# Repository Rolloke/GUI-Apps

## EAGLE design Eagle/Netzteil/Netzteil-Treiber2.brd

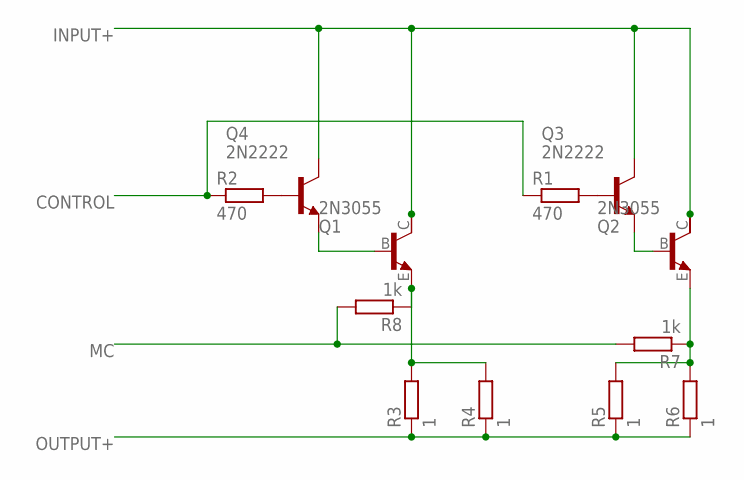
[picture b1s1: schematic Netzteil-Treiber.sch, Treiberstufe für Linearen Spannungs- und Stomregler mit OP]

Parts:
Q1, Q2: 2N3055; TO3
Q3, Q4: 2N2222; TO18
R1, R2: 470; 0207/12
R3, R4, R5, R6: 1; 0207/12
R7, R8: 1k; 0207/12

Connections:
CONTROL: R1.1, R2.1
INPUT+: Q1.C, Q2.C, Q3.3 (C), Q4.3 (C)
MC: R7.2, R8.2
unnamed: Q3.2 (B), R1.2
unnamed: Q4.2 (B), R2.2
unnamed: Q1.E, R3.2, R4.2, R8.1
unnamed: Q1.B, Q4.1 (E)
unnamed: Q2.B, Q3.1 (E)
unnamed: Q2.E, R5.2, R6.2, R7.1
OUTPUT+: R3.1, R4.1, R5.1, R6.1

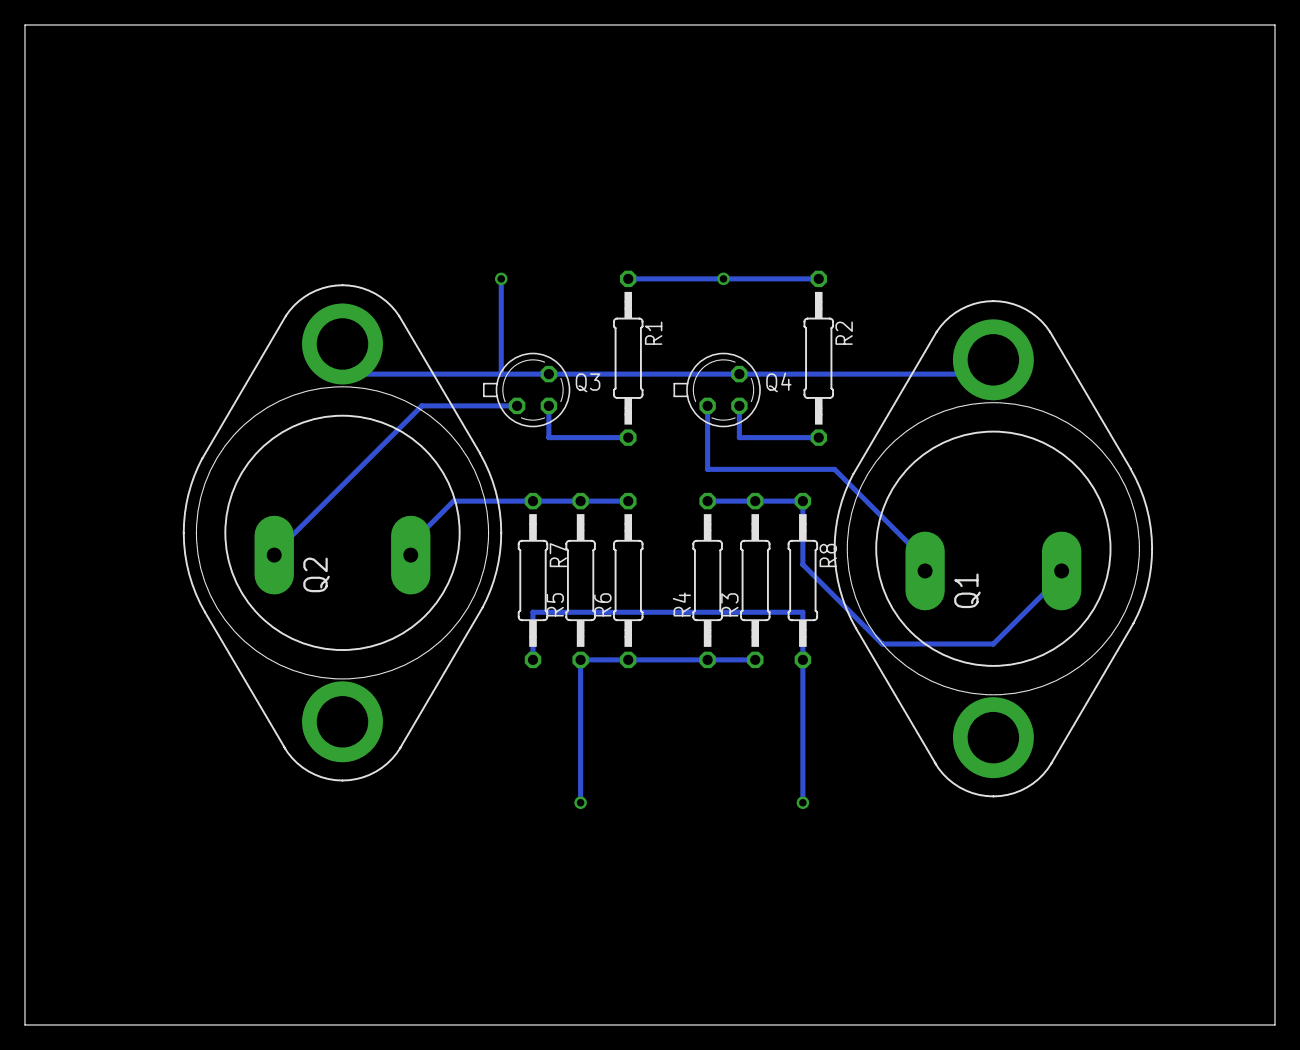
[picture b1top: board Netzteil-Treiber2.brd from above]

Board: 2 copper layers, 100.0 x 80.0 mm, 12 parts (0 on the bottom side), 10 nets.

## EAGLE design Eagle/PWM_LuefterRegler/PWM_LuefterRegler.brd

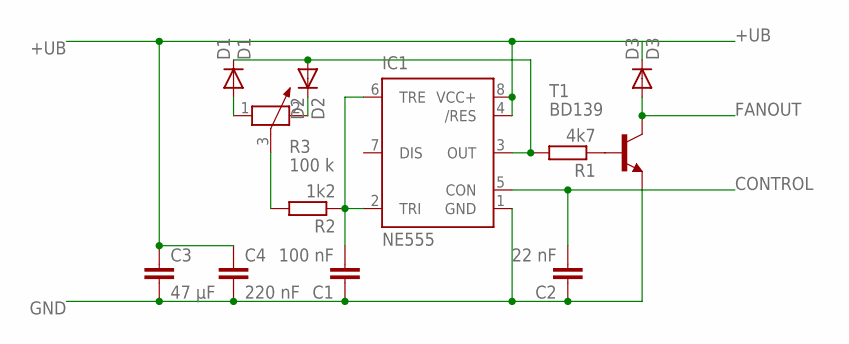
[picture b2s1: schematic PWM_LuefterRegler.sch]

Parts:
C1: 100 nF; C2.5-3
C2: 22 nF; C7.5B3
C3: 47 µF; C5B4.5
C4: 220 nF; C7.5B3
D1: D1; DO35-10
D2: D2; DO35-10
D3: D3; DO35-10
IC1: NE555; DIL-08
R1: 4k7; 0207/10
R2: 1k2; 0207/10
R3: 100 k; PT-10
T1: BD139; TO126

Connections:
+UB: C3.1, C4.1, D3.C, IC1.4 (/RES), IC1.8 (VCC+)
CONTROL: C2.2, IC1.5 (CON)
FANOUT: D3.A, T1.2 (C)
GND: C1.1, C2.1, C3.2, C4.2, IC1.1 (GND), T1.1 (E)
unnamed: C1.2, IC1.2 (TRI), IC1.6 (TRE), R2.1
unnamed: D2.C, R3.2
unnamed: R2.2, R3.3
unnamed: D1.A, R3.1
unnamed: D1.C, D2.A, IC1.3 (OUT), R1.2
unnamed: R1.1, T1.3 (B)

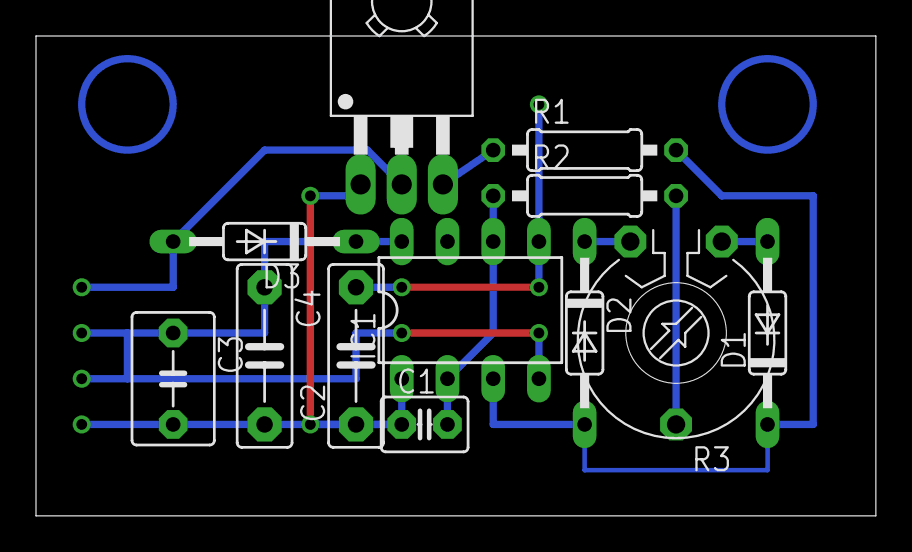
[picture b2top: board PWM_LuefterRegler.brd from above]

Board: 2 copper layers, 46.7 x 26.7 mm, 12 parts (0 on the bottom side), 10 nets.

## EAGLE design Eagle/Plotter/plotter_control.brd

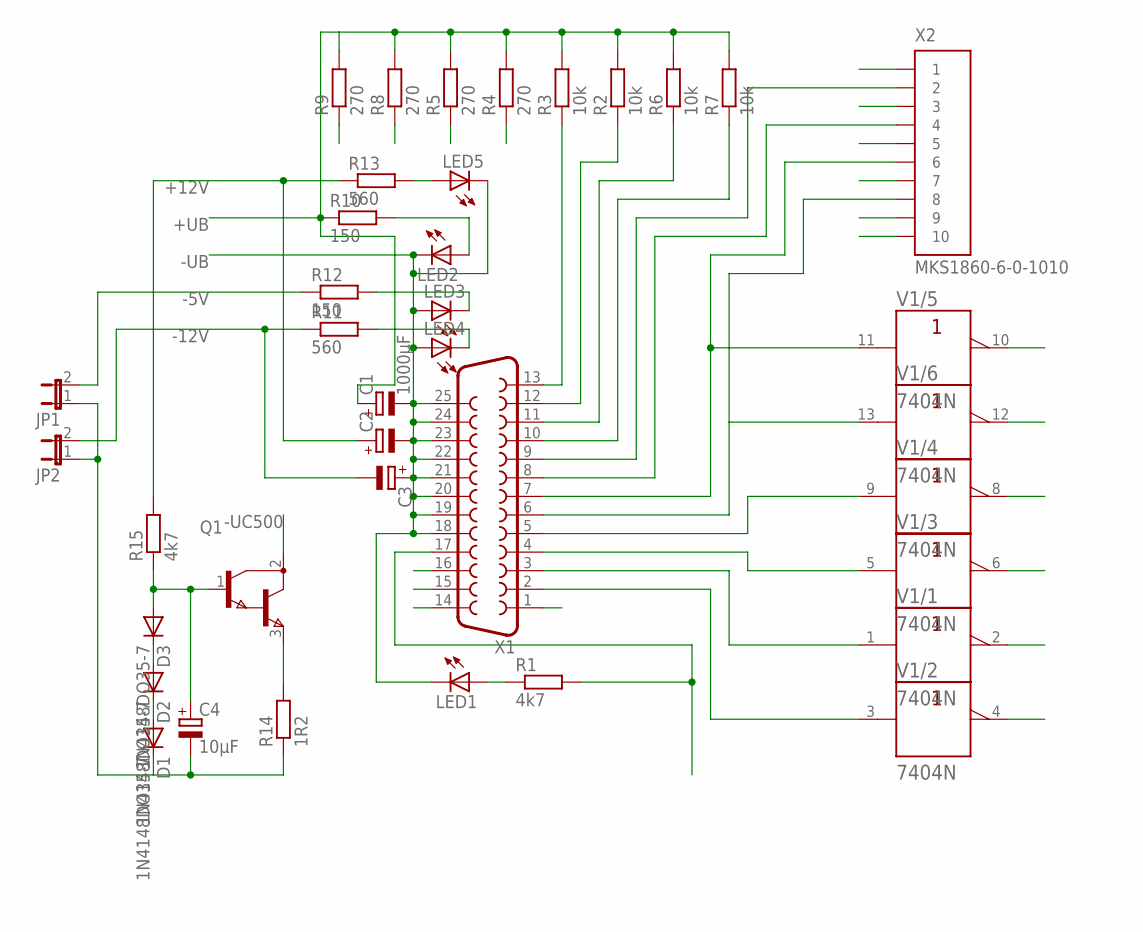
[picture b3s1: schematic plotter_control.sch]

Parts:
C1: 1000µF; E5-8,5
C2, C3: CPOL-EUE5-8.5; E5-8,5
C4: 10µF; E2,5-5
D1, D2, D3: 1N4148DO35-7; DO35-7
JP1, JP2: JP1E; JP1
LED1, LED2, LED3, LED4, LED5: LED3MM
Q1: BD647; TO220
R1, R15: 4k7; 0204/7
R2, R3, R6, R7: 10k; 0204/7
R4, R5, R8, R9: 270; 0204/7
R10: 150; 0207/15
R11, R13: 560; 0204/7
R12: 150; 0207/10
R14: 1R2; 0204/7
V1: 7404N; DIL14
X1: F25HP
X2: MKS1860-6-0-1010

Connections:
+12V: C2.+, R13.1, R15.2
+UB: C1.+, R2.2, R3.2, R4.2, R5.2, R6.2, R7.2, R8.2, R9.2, R10.1, V1.14 (+UB)
-5V: JP1.2, R12.1
-12V: C3.-, JP2.2, R11.1
-UB: C1.-, C2.-, C3.+, LED1.K (C), LED2.K (C), LED3.A, LED4.A, LED5.K (C), V1.7 (-UB), X1.18, X1.19, X1.20, X1.21, X1.22, X1.23, X1.24, X1.25, X2.1, X2.10
-UC500: Q1.2 (C)
-USERVO: C4.-, D1.C, JP1.1, JP2.1, R14.1
BIT7: X1.8, X2.4
BIT8: X1.9, X2.2
BOTTOM_END: R3.1, X1.13
BOTTOM_LED: R4.1
ENABLE_MOTOR: R1.2, X1.17
ERROR: X1.15
INIT_PRINTER: X1.16
LEFT_END: R7.1, X1.10
LEFT_LED: R9.1
M1_1+: V1.3 (A), X1.2
M1_1-: V1.4 (Y)
M1_2+: V1.1 (A), X1.3
M1_2-: V1.2 (Y)
M2_1+: V1.5 (A), X1.4
M2_1-: V1.6 (Y)
M2_2+: V1.9 (A), X1.5
M2_2-: V1.8 (Y)
M3_1+: V1.13 (A), X1.6, X2.8
M3_1-: V1.12 (Y)
M3_2+: V1.11 (A), X1.7, X2.6
M3_2-: V1.10 (Y)
M4_1: X2.9
M4_2: X2.7
M4_3: X2.5
M4_4: X2.3
MOTOR_COIL1: X1.1
MOTOR_COIL2: X1.14
unnamed: LED1.A, R1.1
unnamed: LED2.A, R10.2
unnamed: LED5.A, R13.2
unnamed: LED3.K (C), R12.2
unnamed: LED4.K (C), R11.2
unnamed: D1.A, D2.C
unnamed: D2.A, D3.C
unnamed: Q1.3 (E), R14.2
unnamed: C4.+, D3.A, Q1.1 (B), R15.1
RIGHT_END: R6.1, X1.11
RIGHT_LED: R8.1
TOP_END: R2.1, X1.12
TOP_LED: R5.1

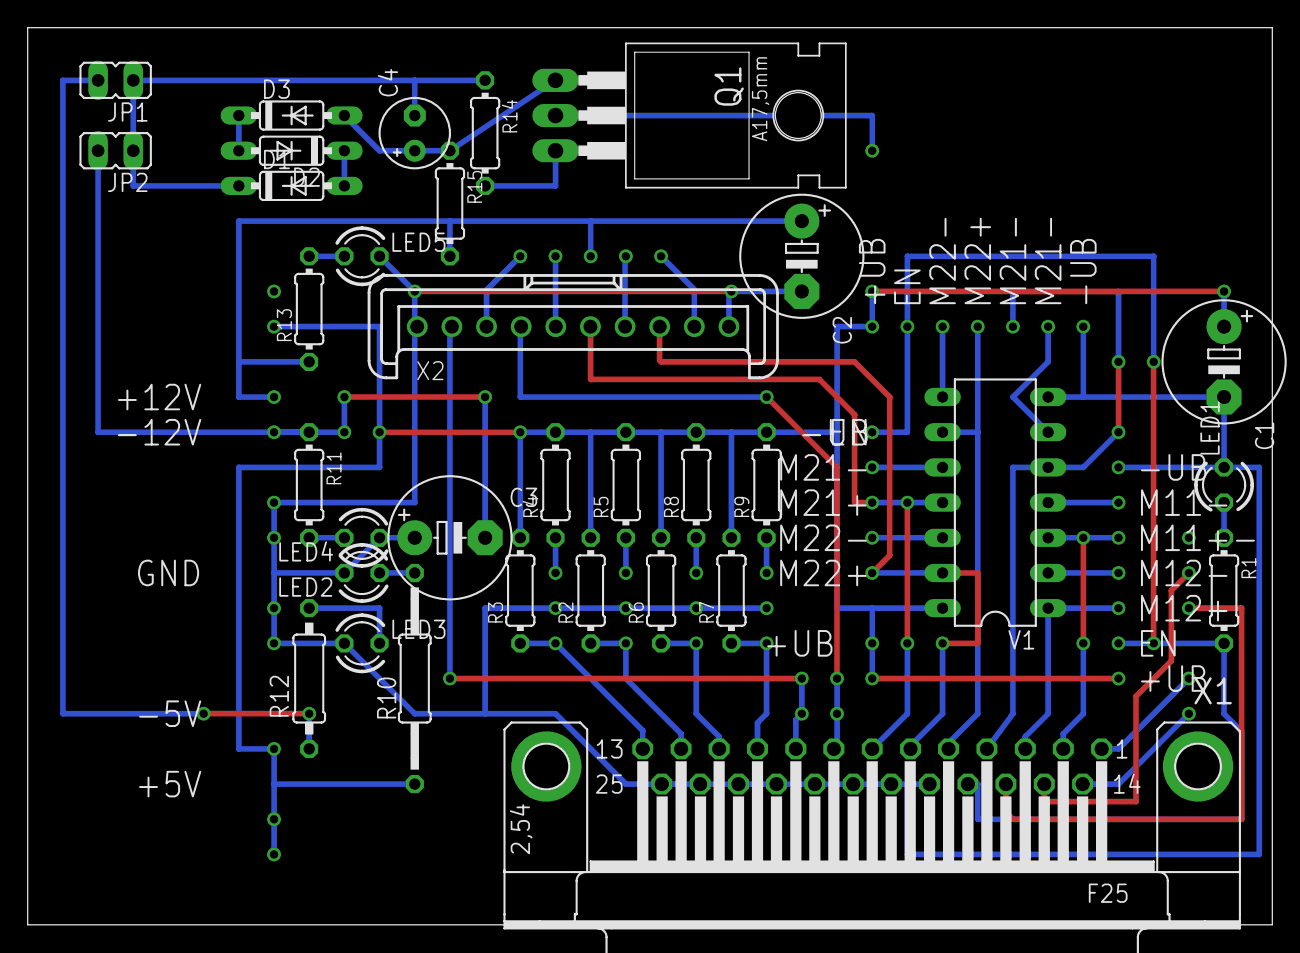
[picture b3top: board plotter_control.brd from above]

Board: 2 copper layers, 89.8 x 64.8 mm, 33 parts (0 on the bottom side), 28 nets.

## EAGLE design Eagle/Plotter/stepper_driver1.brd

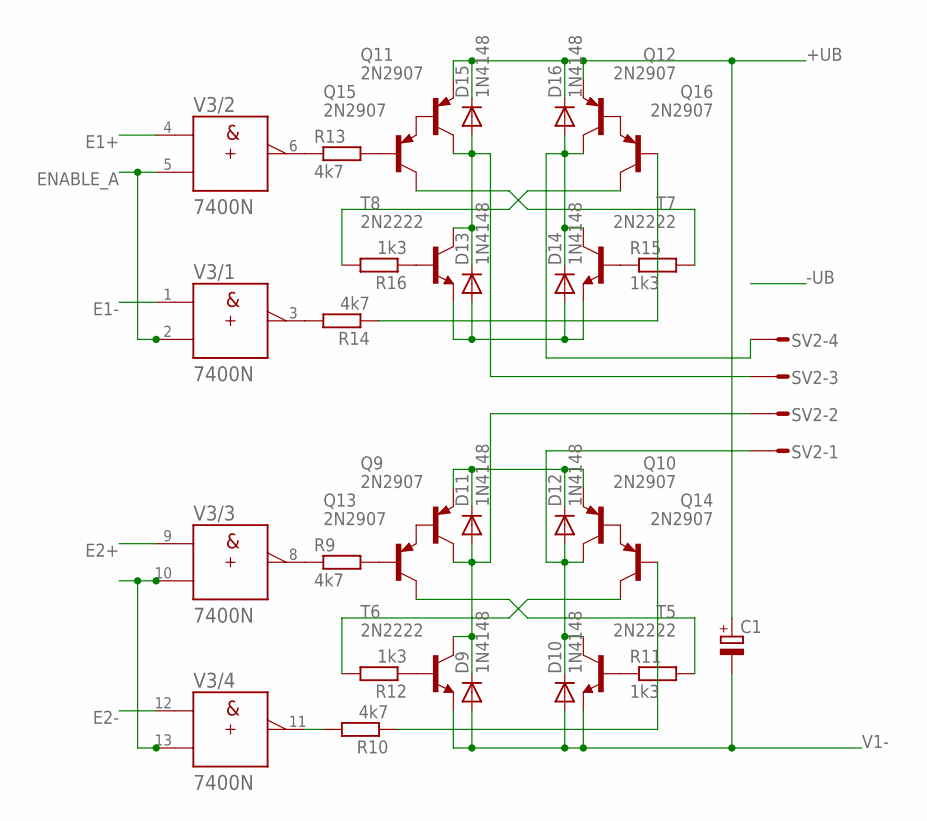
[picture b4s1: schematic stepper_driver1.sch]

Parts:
C1: CPOL-EUE3.5-10; E3,5-10
D9, D10, D11, D12, D13, D14, D15, D16: 1N4148; D-2.5
Q9, Q10, Q11, Q12, Q13, Q14, Q15, Q16: 2N2907; TO18
R9, R13, R14: 4k7; 0207/10
R10: 4k7; 0207/12
R11, R12, R15, R16: 1k3; 0207/10
SV2: S04P
T5, T6, T7, T8: 2N2222; TO18
V3: 7400N; DIL14

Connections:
+UB: C1.+, D11.C, D12.C, D15.C, D16.C, Q9.1 (E), Q10.1 (E), Q11.1 (E), Q12.1 (E), V3.14 (+UB)
-UB: V3.7 (-UB)
A1+: D13.C, D15.A, Q11.3 (C), SV2.3, T8.3 (C)
A1-: D14.C, D16.A, Q12.3 (C), SV2.4, T7.3 (C)
A2+: D9.C, D11.A, Q9.3 (C), SV2.2, T6.3 (C)
A2-: D10.C, D12.A, Q10.3 (C), SV2.1, T5.3 (C)
E1+: V3.4 (A)
E1-: V3.1 (A)
E2+: V3.9 (A)
E2-: V3.12 (A)
ENABLE_A: V3.2 (B), V3.5 (B)
ENABLE_B: V3.10 (B), V3.13 (B)
unnamed: Q14.3 (C), R12.2
unnamed: Q14.2 (B), R10.1
unnamed: Q13.3 (C), R11.2
unnamed: R9.1, V3.8 (Y)
unnamed: R10.2, V3.11 (Y)
unnamed: Q16.3 (C), R16.2
unnamed: Q16.2 (B), R14.1
unnamed: Q15.3 (C), R15.2
unnamed: R14.2, V3.3 (Y)
unnamed: R13.1, V3.6 (Y)
unnamed: R12.1, T6.2 (B)
unnamed: R11.1, T5.2 (B)
unnamed: Q9.2 (B), Q13.1 (E)
unnamed: Q10.2 (B), Q14.1 (E)
unnamed: R16.1, T8.2 (B)
unnamed: R15.1, T7.2 (B)
unnamed: Q11.2 (B), Q15.1 (E)
unnamed: Q12.2 (B), Q16.1 (E)
unnamed: Q15.2 (B), R13.2
unnamed: Q13.2 (B), R9.2
V1-: C1.-, D9.A, D10.A, D13.A, D14.A, T5.1 (E), T6.1 (E), T7.1 (E), T8.1 (E)

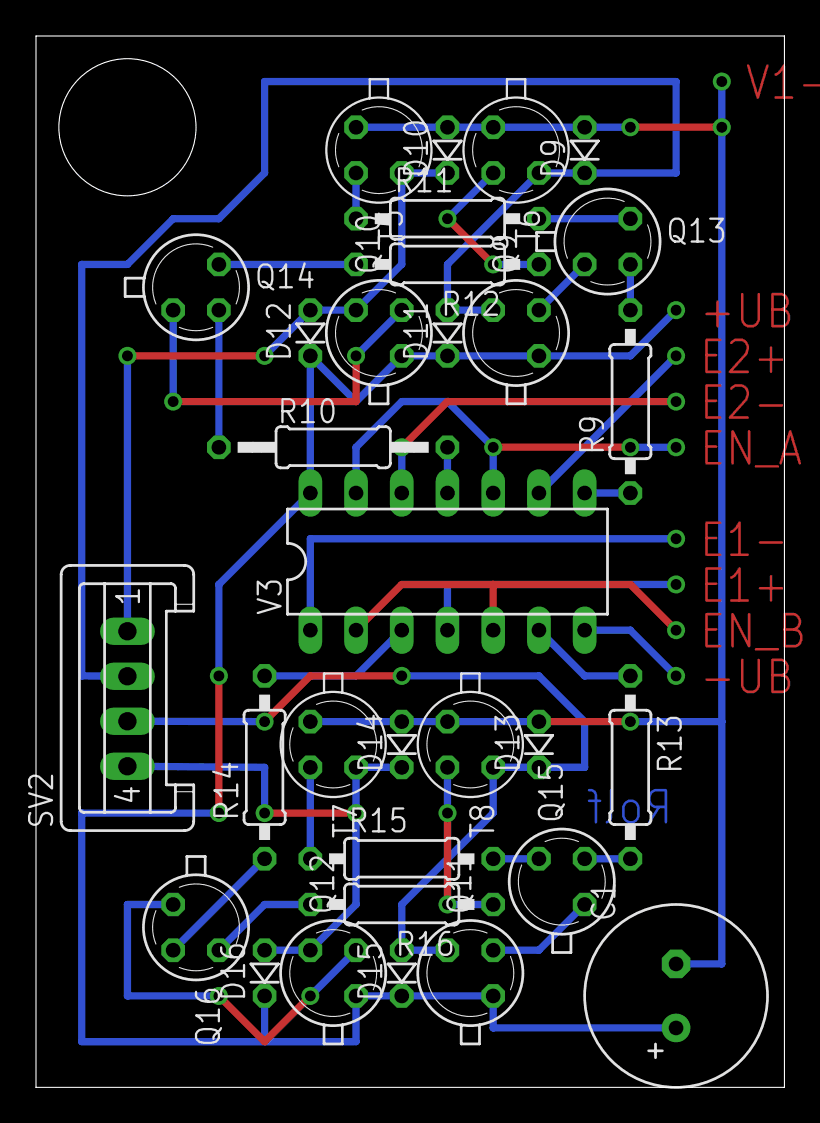
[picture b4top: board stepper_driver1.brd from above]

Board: 2 copper layers, 41.6 x 58.4 mm, 31 parts (0 on the bottom side), 28 nets.

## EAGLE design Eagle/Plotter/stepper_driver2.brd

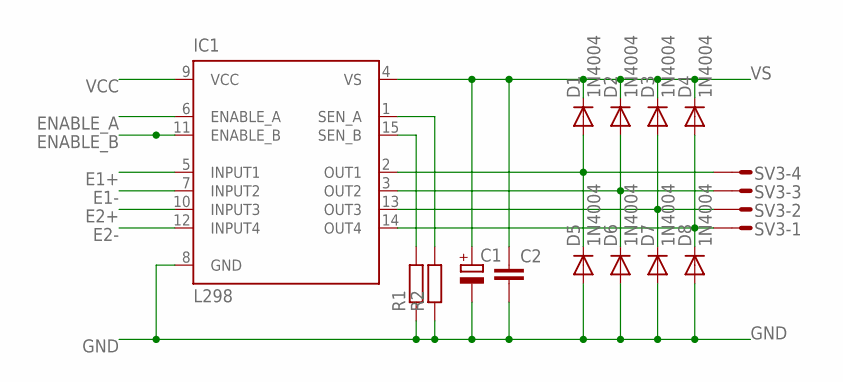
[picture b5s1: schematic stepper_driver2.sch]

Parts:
C1: CPOL-EUE3.5-10; E3,5-10
C2: C-EU050-025X075; C050-025X075
D1, D2, D3, D4, D5, D6, D7, D8: 1N4004; DO41-10
IC1: L298; MULTIWATT-15
R1, R2: R-EU_0207/15; 0207/15
SV3: S04P

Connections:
A1+: D1.A, D5.C, IC1.2 (OUT1), SV3.4
A1-: D2.A, D6.C, IC1.3 (OUT2), SV3.3
A2+: D3.A, D7.C, IC1.13 (OUT3), SV3.2
A2-: D4.A, D8.C, IC1.14 (OUT4), SV3.1
E1+: IC1.5 (INPUT1)
E1-: IC1.7 (INPUT2)
E2+: IC1.10 (INPUT3)
E2-: IC1.12 (INPUT4)
ENABLE_A: IC1.6 (ENABLE_A)
ENABLE_B: IC1.11 (ENABLE_B)
GND: C1.-, C2.2, D5.A, D6.A, D7.A, D8.A, IC1.8 (GND), R1.1, R2.1
unnamed: IC1.15 (SEN_B), R1.2
unnamed: IC1.1 (SEN_A), R2.2
VCC: IC1.9 (VCC)
VS: C1.+, C2.1, D1.C, D2.C, D3.C, D4.C, IC1.4 (VS)

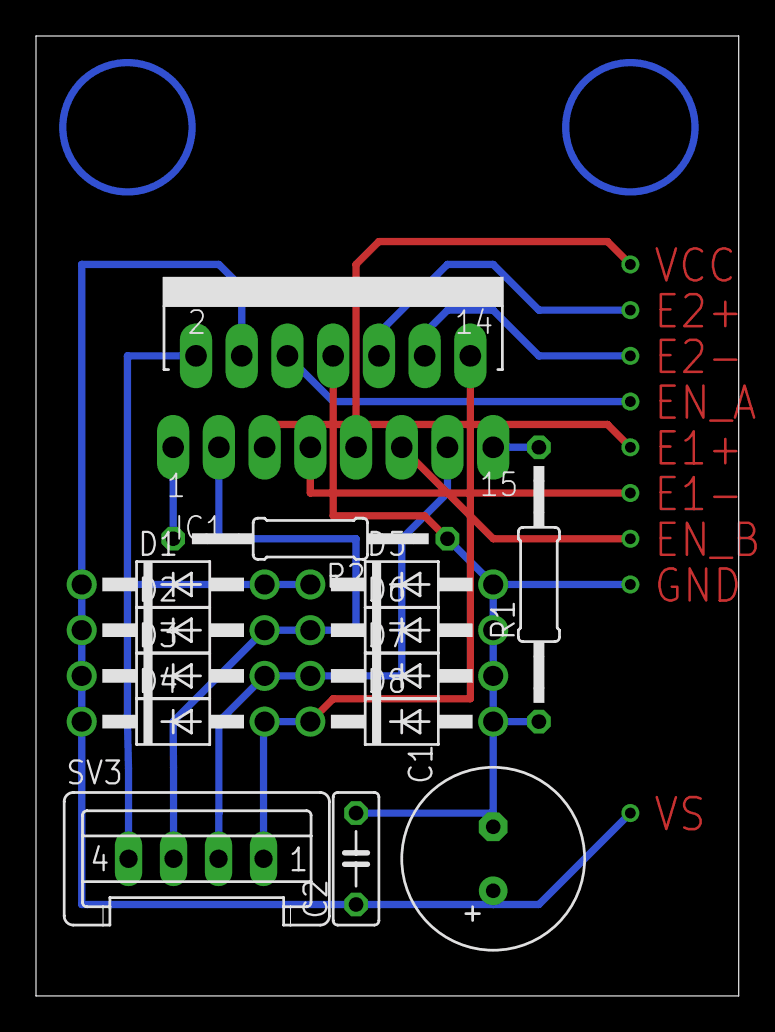
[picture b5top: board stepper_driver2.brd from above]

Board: 2 copper layers, 39.0 x 53.3 mm, 14 parts (0 on the bottom side), 8 nets.
